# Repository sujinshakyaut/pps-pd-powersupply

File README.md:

# USB-CPS Power Supply

## Highlights

- USB-C Power Delivery breakout board based on the **PPS protocol** and PD capabilities of USB-C.
- Programmable, regulated output from **5 V to 24 V**
- Dynamic voltage and current negotiation with **PD-compliant chargers**
- Simple **I²C interface** for configuration and real-time monitoring
- Built-in protection by AP33772S: **OVP, UVP, OCP, and OTP**

---

## Libraries

- [Arduino Library (CentyLab)](https://github.com/CentyLab/AP33772S-CentyLab?utm_source=chatgpt.com)

- [AP33772S PD Controller Sink Datasheet (Diodes Inc)](https://www.diodes.com/datasheet/download/AP33772S.pdf?utm_source=chatgpt.com)  
- [Breakout Board Evaluation Board Guide)](https://www.diodes.com/assets/Evaluation-Boards/AP33772S-Sink-Controller-EVB-User-Guide.pdf)

---

## Requirements for AVS

To utilize the **AVS (Adjustable Voltage Supply)** profile, you need a **USB-C charger or power bank that supports AVS** and a **high-power USB-C cable rated for at least 240 W**. Compatible devices we have tested include:

- **Framework Laptop Charger** – 180 W  
- **AMEGAT Powerbank** – 140 W  
- **Baseus Powerbank** – 140 W  
- **UGREEN Nexode** – 300 W  

Using a non-AVS charger or an insufficient cable may prevent proper voltage negotiation or limit maximu

## Description

The **I²C-Enabled USB-C Power Supply** is a programmable DC power source built around the **AP33772S USB Type-C® PD 3.1 sink controller**. It converts a standard USB-C Power Delivery adapter into an adjustable output supply, supporting **PPS (up to 21 V)** and **EPR/AVS (up to 28 V)** for flexible, standards-compliant power delivery.

All USB-PD negotiation is handled by the AP33772S, allowing an external microcontroller to configure voltage, current, and protection thresholds through a simple **I²C interface**—no USB-PD firmware required. The board integrates essential safety features including **OVP, UVP, OCP, OTP** and external NTC-based thermal monitoring.

Status feedback is provided via an onboard **PD status LED**, making the board well suited for programmable power supplies, embedded systems, and USB-C PD development.

---

## Easy I²C Control

The board exposes a **register-based I²C interface** for full configuration and monitoring. The host MCU can programmatically:

- Set precise output voltage and current limits according to the PD contract  
- Query negotiated PD parameters, including voltage, current, and power delivery status  
- Monitor real-time fault conditions and protection events (OVP, UVP, OCP, OTP)  

All USB-PD negotiation and safety enforcement are managed internally by the **AP33772S**, allowing the MCU to focus on application-level control without handling the PD protocol stack.

---

Specifications

- **Output Voltage:** 5 V – 24 V (PPS), dynamically adjustable via I²C  
- **Power Delivery Support:** USB-C PD 3.1 with PPS and SPR/EPR profiles  
- **Maximum Current:** Dependent on PD contract and charger capabilities  
- **Protection Features:** Over-Voltage (OVP), Under-Voltage (UVP), Over-Current (OCP), Over-Temperature (OTP)  
- **Control Interface:** I²C (register-based) for configuration and monitoring  
- **Input Source:** USB-C PD-compliant charger  
- **Status Indicators:** LED for PD negotiation, FLIP pin for cable orientation detection

---

## Author

**Sujin Shakya**  
GitHub: https://github.com/sujinshakyaut

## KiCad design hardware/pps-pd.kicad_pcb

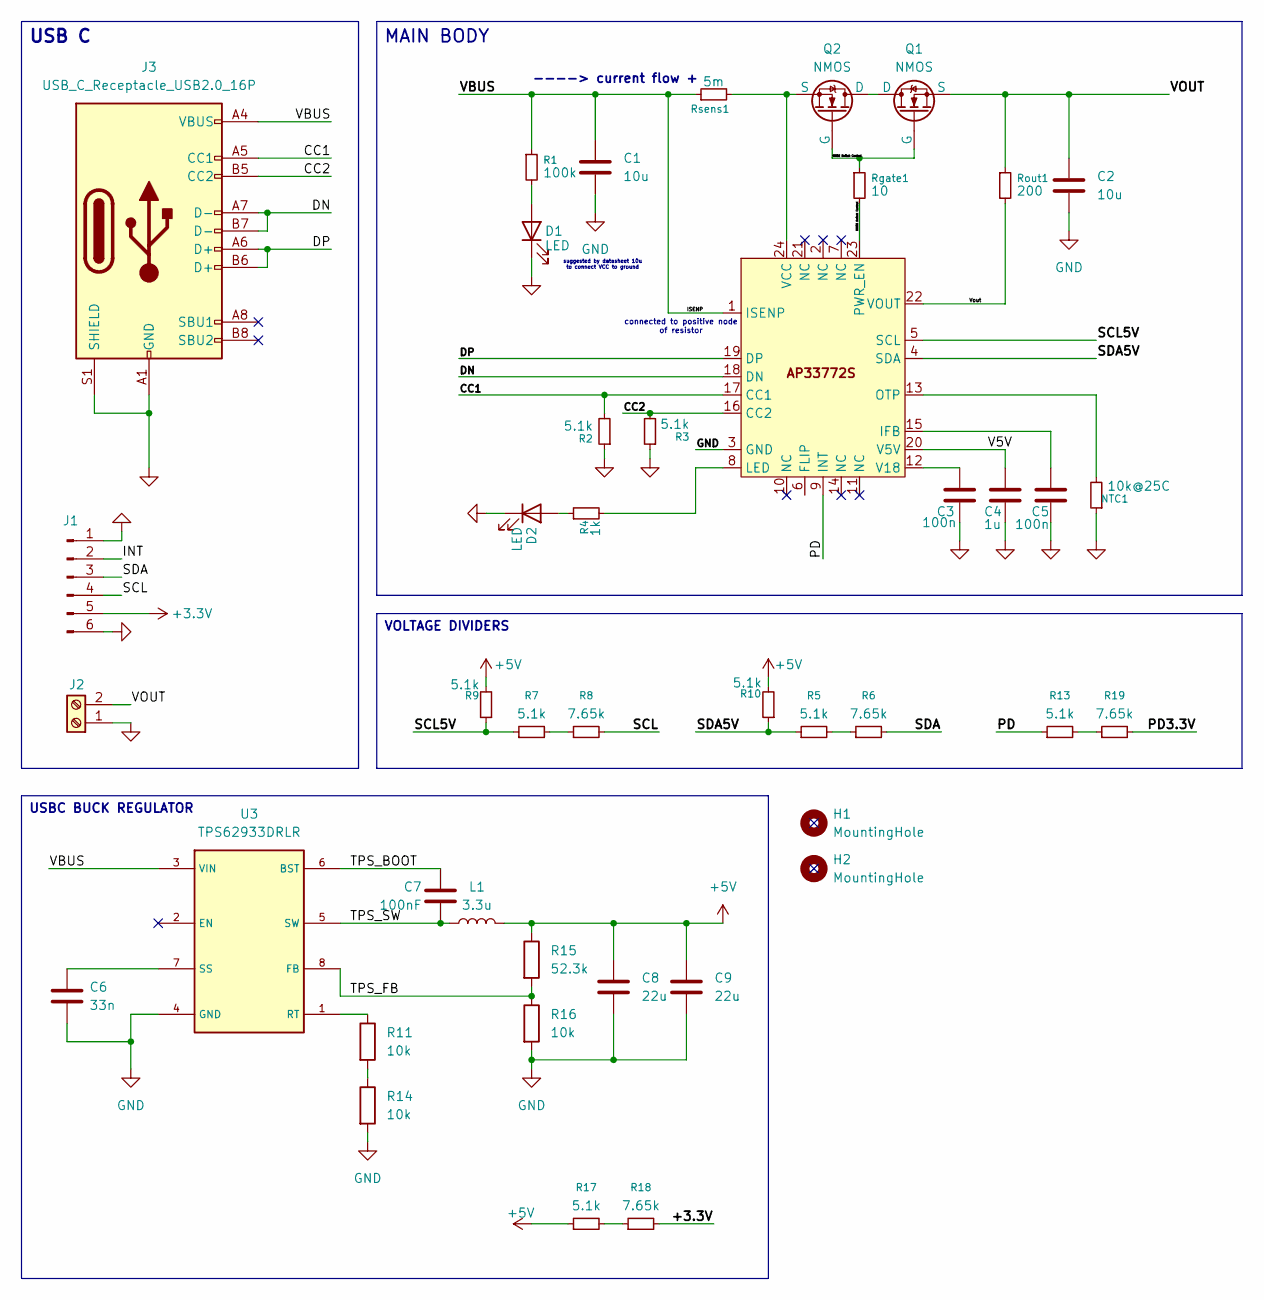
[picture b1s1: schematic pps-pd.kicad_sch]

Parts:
C1, C2: 10u; C_0402_1005Metric
C3, C5: 100n; C_0402_1005Metric
C4: 1u; C_0402_1005Metric
C6: 33n; C_0603_1608Metric; LCSC C21117
C7: 100nF; C_0402_1005Metric; LCSC C1525
C8, C9: 22u; C_0805_2012Metric; LCSC C45783
D1, D2: LED; LED_0603_1608Metric
H1, H2: MountingHole; MountingHole_2.7mm_M2.5_DIN965_Pad_TopBottom
J1: Conn_01x06_Pin; PinHeader_1x08_P2.54mm_Vertical
J2: Screw_Terminal_5mm; TerminalBlock_Phoenix_MKDS-1,5-2_1x02_P5.00mm_Horizontal
J3: USB_C_Receptacle_USB2.0_16P; USB_C_Receptacle_GCT_USB4105-xx-A_16P_TopMnt_Horizontal
L1: 3.3u; L_Bourns_SRP7028A_7.3x6.6mm
NTC1: 10k@25C; R_0402_1005Metric
Q1, Q2: NMOS; DFN-8-1EP_3x3mm_P0.5mm_EP1.65x2.38mm
R1: 100k; R_0402_1005Metric
R2, R3, R5, R7, R9, R10, R13, R17: 5.1k; R_0402_1005Metric
R4: 1k; R_0402_1005Metric
R6, R8, R18, R19: 7.65k; R_0402_1005Metric
R11, R14, R16: 10k; R_0402_1005Metric; LCSC C25744
R15: 52.3k; R_0402_1005Metric; LCSC C103091
Rgate1: 10; R_0402_1005Metric
Rout1: 200; R_0402_1005Metric
Rsens1: 5m; R_0402_1005Metric
U1: AP33772S; PD Sink IC
U3: TPS62933DRLR; SOT-583-8

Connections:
+3.3V: J1.5, R18.2
+5V: C8.1, C9.1, L1.2, R9.2, R10.2, R15.1, R17.1
/CC1: J3.A5 (CC1), R2.2, U1.17 (CC1)
/CC2: J3.B5 (CC2), R3.2, U1.16 (CC2)
/DN: J3.A7 (D-), J3.B7 (D-), U1.18 (DN)
/DP: J3.A6 (D+), J3.B6 (D+), U1.19 (DP)
/INT: J1.2
/ISENP: C1.1, J3.A4 (VBUS), J3.A9 (VBUS), J3.B4 (VBUS), J3.B9 (VBUS), R1.1, Rsens1.1, U1.1 (ISENP), U3.3 (VIN)
/NMOS Switch Control: Q1.2 (G), Q2.2 (G), Rgate1.1, Rgate1.2, U1.23 (PWR_EN)
/PD: R13.1, U1.9 (INT)
/PD3.3V: R19.2
/SCL: J1.4, R8.2
/SCL5V: R7.1, R9.1, U1.5 (SCL)
/SDA: J1.3, R6.2
/SDA5V: R5.1, R10.1, U1.4 (SDA)
/TPS_BOOT: C7.1, U3.6 (BST)
/TPS_FB: R15.2, R16.1, U3.8 (FB)
/TPS_SW: C7.2, L1.1, U3.5 (SW)
/V5V: C4.1, U1.20 (V5V)
/VOUT: C2.1, J2.2, Q1.3 (S), Rout1.1
/Vout: Rout1.2, U1.22 (VOUT)
GND: C1.2, C2.2, C3.2, C4.2, C5.2, C6.2, C8.2, C9.2, D1.1 (K), D2.1 (K), J1.1, J1.6, J2.1, J3.A1 (GND), J3.A12 (GND), J3.B1 (GND), J3.B12 (GND), J3.S1 (SHIELD), NTC1.1, R2.1, R3.1, R14.2, R16.2, U1.3 (GND), U3.4 (GND)
unnamed: D1.2 (A), R1.2
unnamed: D2.2 (A), R4.1
unnamed: Q1.1 (D), Q2.1 (D)
unnamed: Q2.3 (S), Rsens1.2, U1.24 (VCC)
unnamed: R5.2, R6.1
unnamed: R7.2, R8.1
unnamed: R11.2, R14.1
unnamed: R13.2, R19.1
unnamed: R17.2, R18.1
unnamed: C5.1, U1.15 (IFB)
unnamed: R4.2, U1.8 (LED)
unnamed: NTC1.2, U1.13 (OTP)
unnamed: C3.1, U1.12 (V18)
unnamed: R11.1, U3.1 (RT)
unnamed: C6.1, U3.7 (SS)

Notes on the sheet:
----> current flow +
connected to positive node of resistor
suggested by datasheet 10u to connect VCC to ground
MAIN BODY
USBC BUCK REGULATOR
VOLTAGE DIVIDERS
USB C

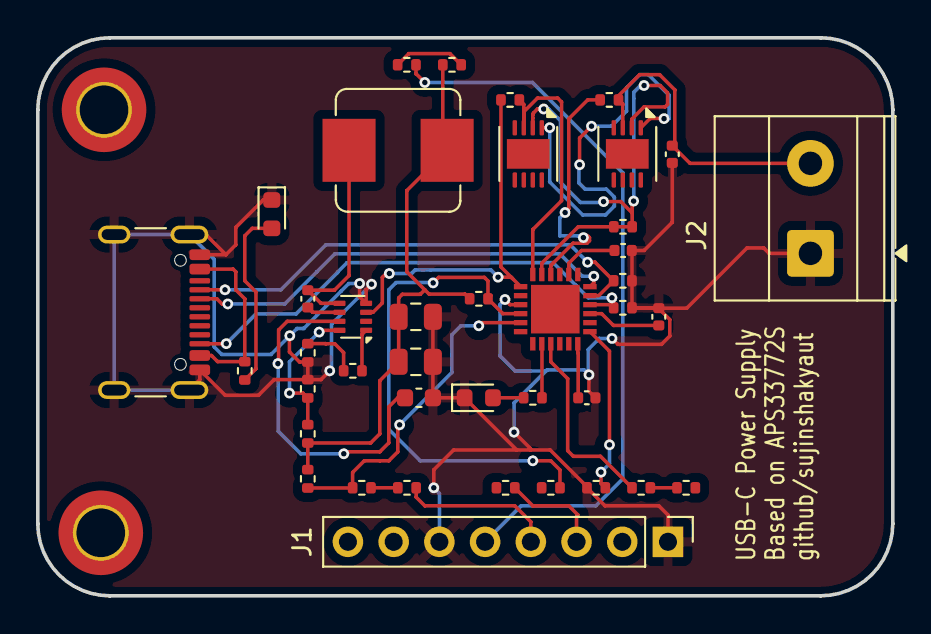
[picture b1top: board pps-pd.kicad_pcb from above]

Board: 2 copper layers, 47.5 x 31.0 mm, 42 parts (0 on the bottom side), 35 nets.

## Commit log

2025-12-28 adding files
2025-12-28 kicad files
2026-01-07 V1-demo-breakout
    test board
2026-01-09 final update
    fixed layout issues
2026-01-10 Add linguist-vendored setting for dist directory
2026-01-10 Update .gitattributes for linguist detection
